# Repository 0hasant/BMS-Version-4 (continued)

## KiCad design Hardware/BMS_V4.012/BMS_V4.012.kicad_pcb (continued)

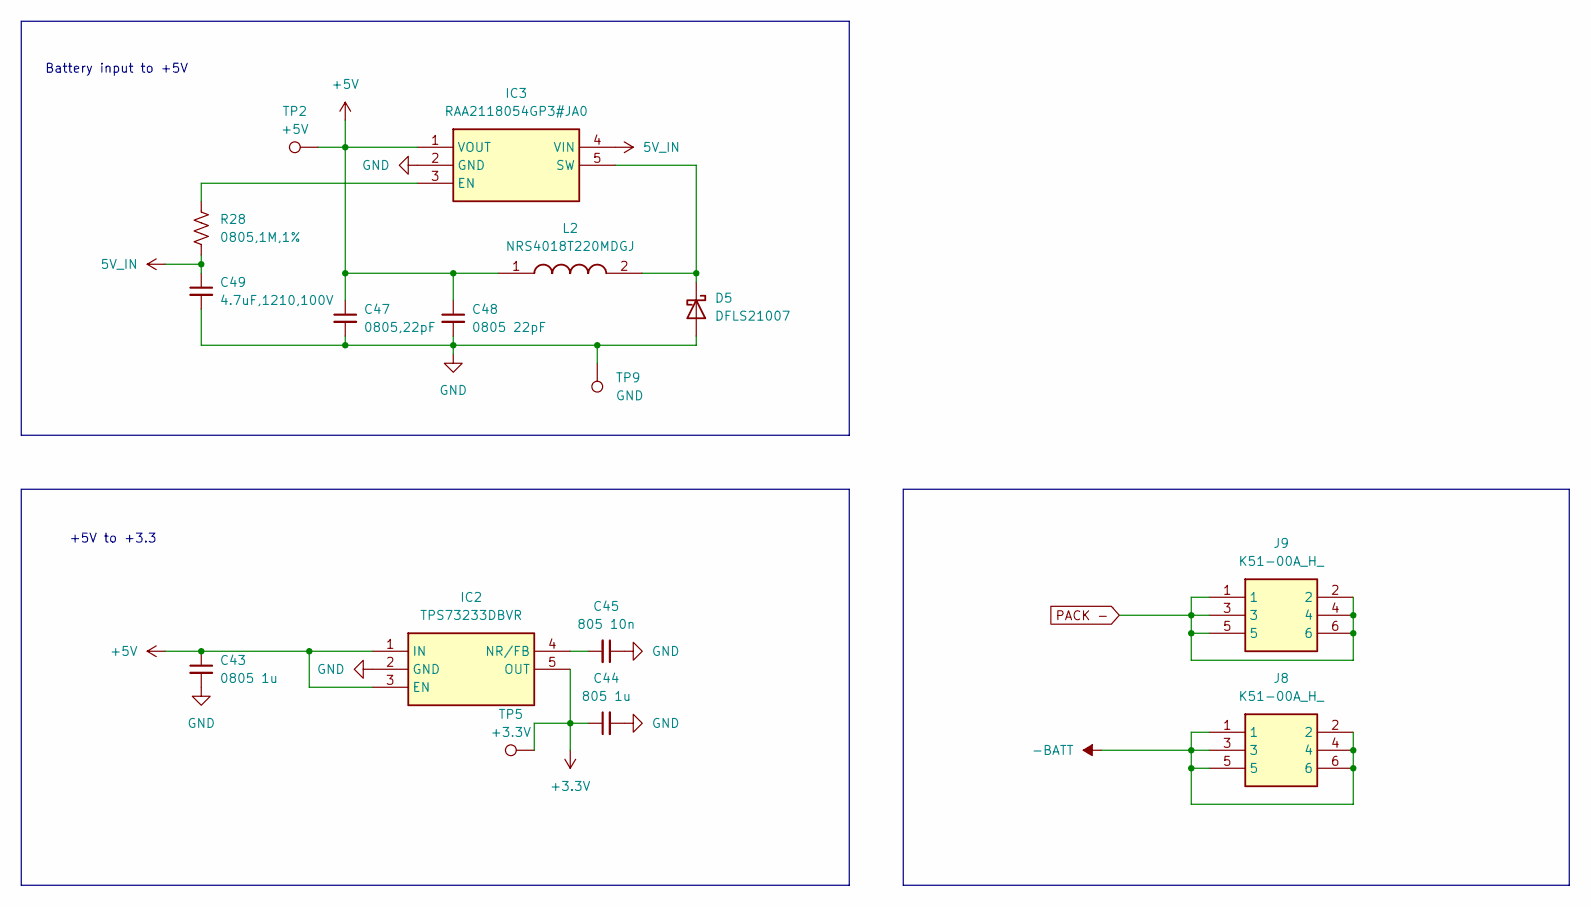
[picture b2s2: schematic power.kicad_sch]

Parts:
C43: 0805 1u; CAPC2012X94N
C44: 805 1u; CAPC2012X94N
C45: 805 10n; CAPC2012X94N
C47: 0805,22pF; CAPC2012X94N
C48: 0805 22pF; CAPC2012X94N
C49: 4.7uF,1210,100V; C_1210_3225Metric
D5: DFLS21007
IC2: TPS73233DBVR; SOT95P280X145-5N; Manufacturer_Part_Number TPS73233DBVR; Mouser Part Number 595-TPS73233DBVR
IC3: RAA2118054GP3#JA0; SOT95P280X110-5N; Manufacturer_Part_Number RAA2118054GP3#JA0; Mouser Part Number 968-RAA2118054GP3JA0
J8, J9: K51-00A_H_; K5100AH; Manufacturer_Part_Number K51-00A(H)
L2: NRS4018T220MDGJ; Manufacturer_Part_Number NRS4018T220MDGJ; Mouser Part Number 963-NRS4018T220MDGJ
R28: 0805,1M,1%; RES_ERA6AHD330V
TP2: +5V; TestPoint_THTPad_D1.0mm_Drill0.5mm
TP5: +3.3V; TestPoint_THTPad_D1.0mm_Drill0.5mm
TP9: GND; TestPoint_2Pads_Pitch5.08mm_Drill1.3mm

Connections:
5V_IN: C49.1, IC3.4 (VIN), R28.2; also elsewhere on the board
+3.3V: C44.1, IC2.5 (OUT), TP5.1; also elsewhere on the board
+5V: C43.1, C47.1, C48.1, IC2.1 (IN), IC2.3 (EN), IC3.1 (VOUT), L2.1, TP2.1; also elsewhere on the board
-BATT: J8.1, J8.2, J8.3, J8.4, J8.5, J8.6; also elsewhere on the board
GND: C43.2, C44.2, C45.1, C47.2, C48.2, C49.2, D5.2 (A), IC2.2 (GND), IC3.2 (GND), TP9.1; also elsewhere on the board
unnamed: D5.1 (K), IC3.5 (SW), L2.2
unnamed: C45.2, IC2.4 (NR/FB)
unnamed: IC3.3 (EN), R28.1
PACK -: J9.1, J9.2, J9.3, J9.4, J9.5, J9.6; also elsewhere on the board

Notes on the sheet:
+5V to +3.3
Battery input to +5V

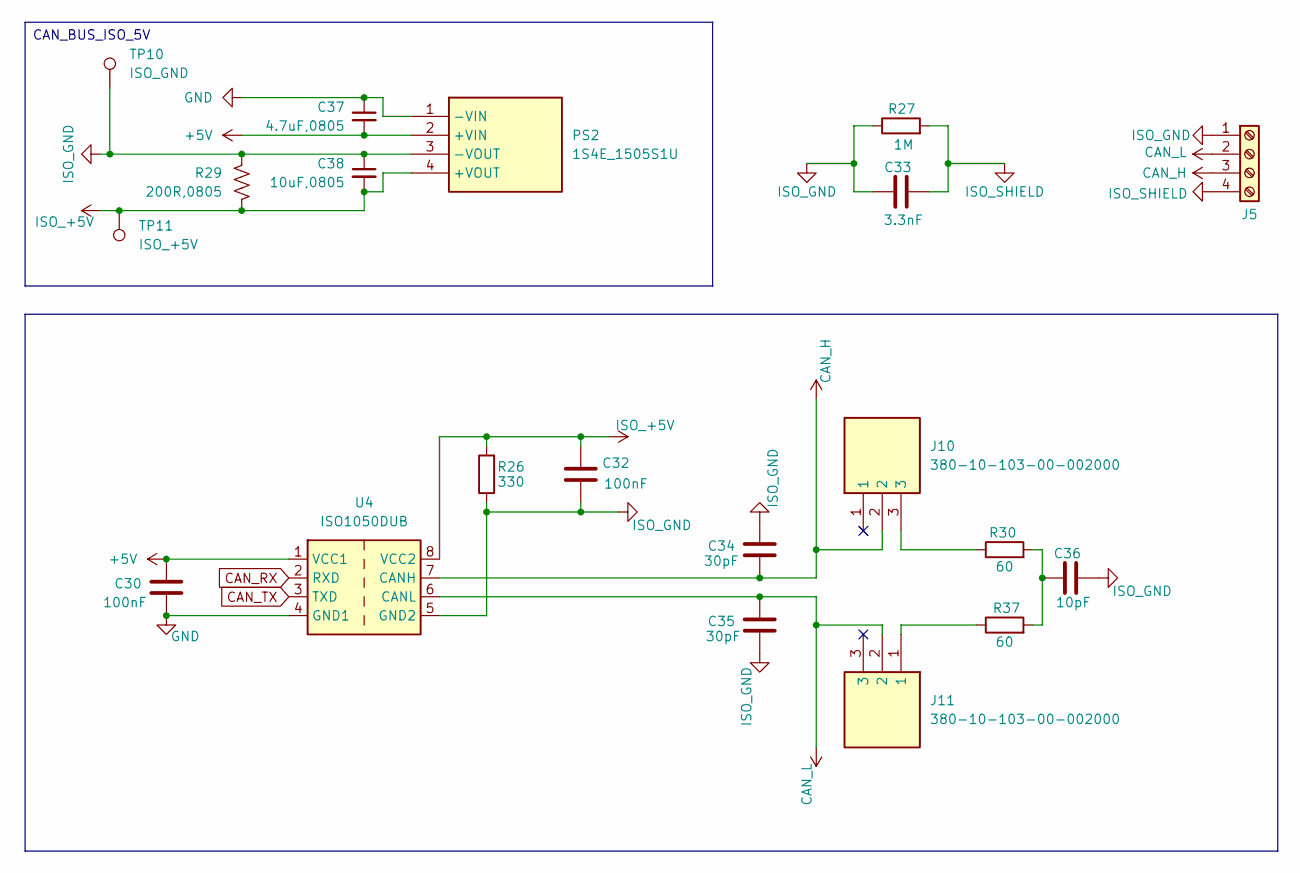
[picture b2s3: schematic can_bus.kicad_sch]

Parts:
C30, C32: 100nF; C_0805_2012Metric_Pad1.18x1.45mm_HandSolder
C33: 3.3nF; C_Disc_D10.5mm_W5.0mm_P5.00mm
C34, C35: 30pF; C_0805_2012Metric_Pad1.18x1.45mm_HandSolder
C36: 10pF; C_0805_2012Metric_Pad1.18x1.45mm_HandSolder
C37: 4.7uF,0805; CAPC2012X94N
C38: 10uF,0805; CAPC2012X94N
J5: Screw_Terminal_01x04; TerminalBlock_Phoenix_MKDS-1,5-4-5.08_1x04_P5.08mm_Horizont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
J10, J11: 380-10-103-00-002000; HDRV3W51P0X254_1X3_762X254X470P; Manufacturer_Part_Number 380-10-103-00-002000; Mouser Part Number 575-3801010300002000
PS2: 1S4E_1505S1U; 1S4E_0303S1U; Manufacturer_Part_Number 1S4E_1505S1U
R26: 330; R_0805_2012Metric_Pad1.20x1.40mm_HandSolder
R27: 1M; R_0805_2012Metric_Pad1.20x1.40mm_HandSolder
R29: 200R,0805; LED_0805_2012Metric_Pad1.15x1.40mm_HandSolder
R30, R37: 60; R_0805_2012Metric_Pad1.20x1.40mm_HandSolder
TP10: ISO_GND; TestPoint_THTPad_D1.0mm_Drill0.5mm
TP11: ISO_+5V; TestPoint_THTPad_D1.0mm_Drill0.5mm
U4: ISO1050DUB; SOP-8_6.62x9.15mm_P2.54mm

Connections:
+5V: C30.1, C37.2, PS2.2 (+VIN), U4.1 (VCC1); also elsewhere on the board
CAN_H: C34.2, J5.3, J10.2, U4.7 (CANH)
CAN_L: C35.1, J5.2, J11.2, U4.6 (CANL)
CAN_RX: U4.2 (RXD); also elsewhere on the board
CAN_TX: U4.3 (TXD); also elsewhere on the board
GND: C30.2, C37.1, PS2.1 (-VIN), U4.4 (GND1); also elsewhere on the board
ISO_+5V: C32.1, C38.2, PS2.4 (+VOUT), R26.2, R29.2, TP11.1, U4.8 (VCC2)
ISO_GND: C32.2, C33.1, C34.1, C35.2, C36.2, C38.1, J5.1, PS2.3 (-VOUT), R26.1, R27.1, R29.1, TP10.1, U4.5 (GND2)
ISO_SHIELD: C33.2, J5.4, R27.2
unnamed: C36.1, R30.2, R37.2
unnamed: J10.3, R30.1
unnamed: J11.1, R37.1

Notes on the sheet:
CAN_BUS_ISO_5V

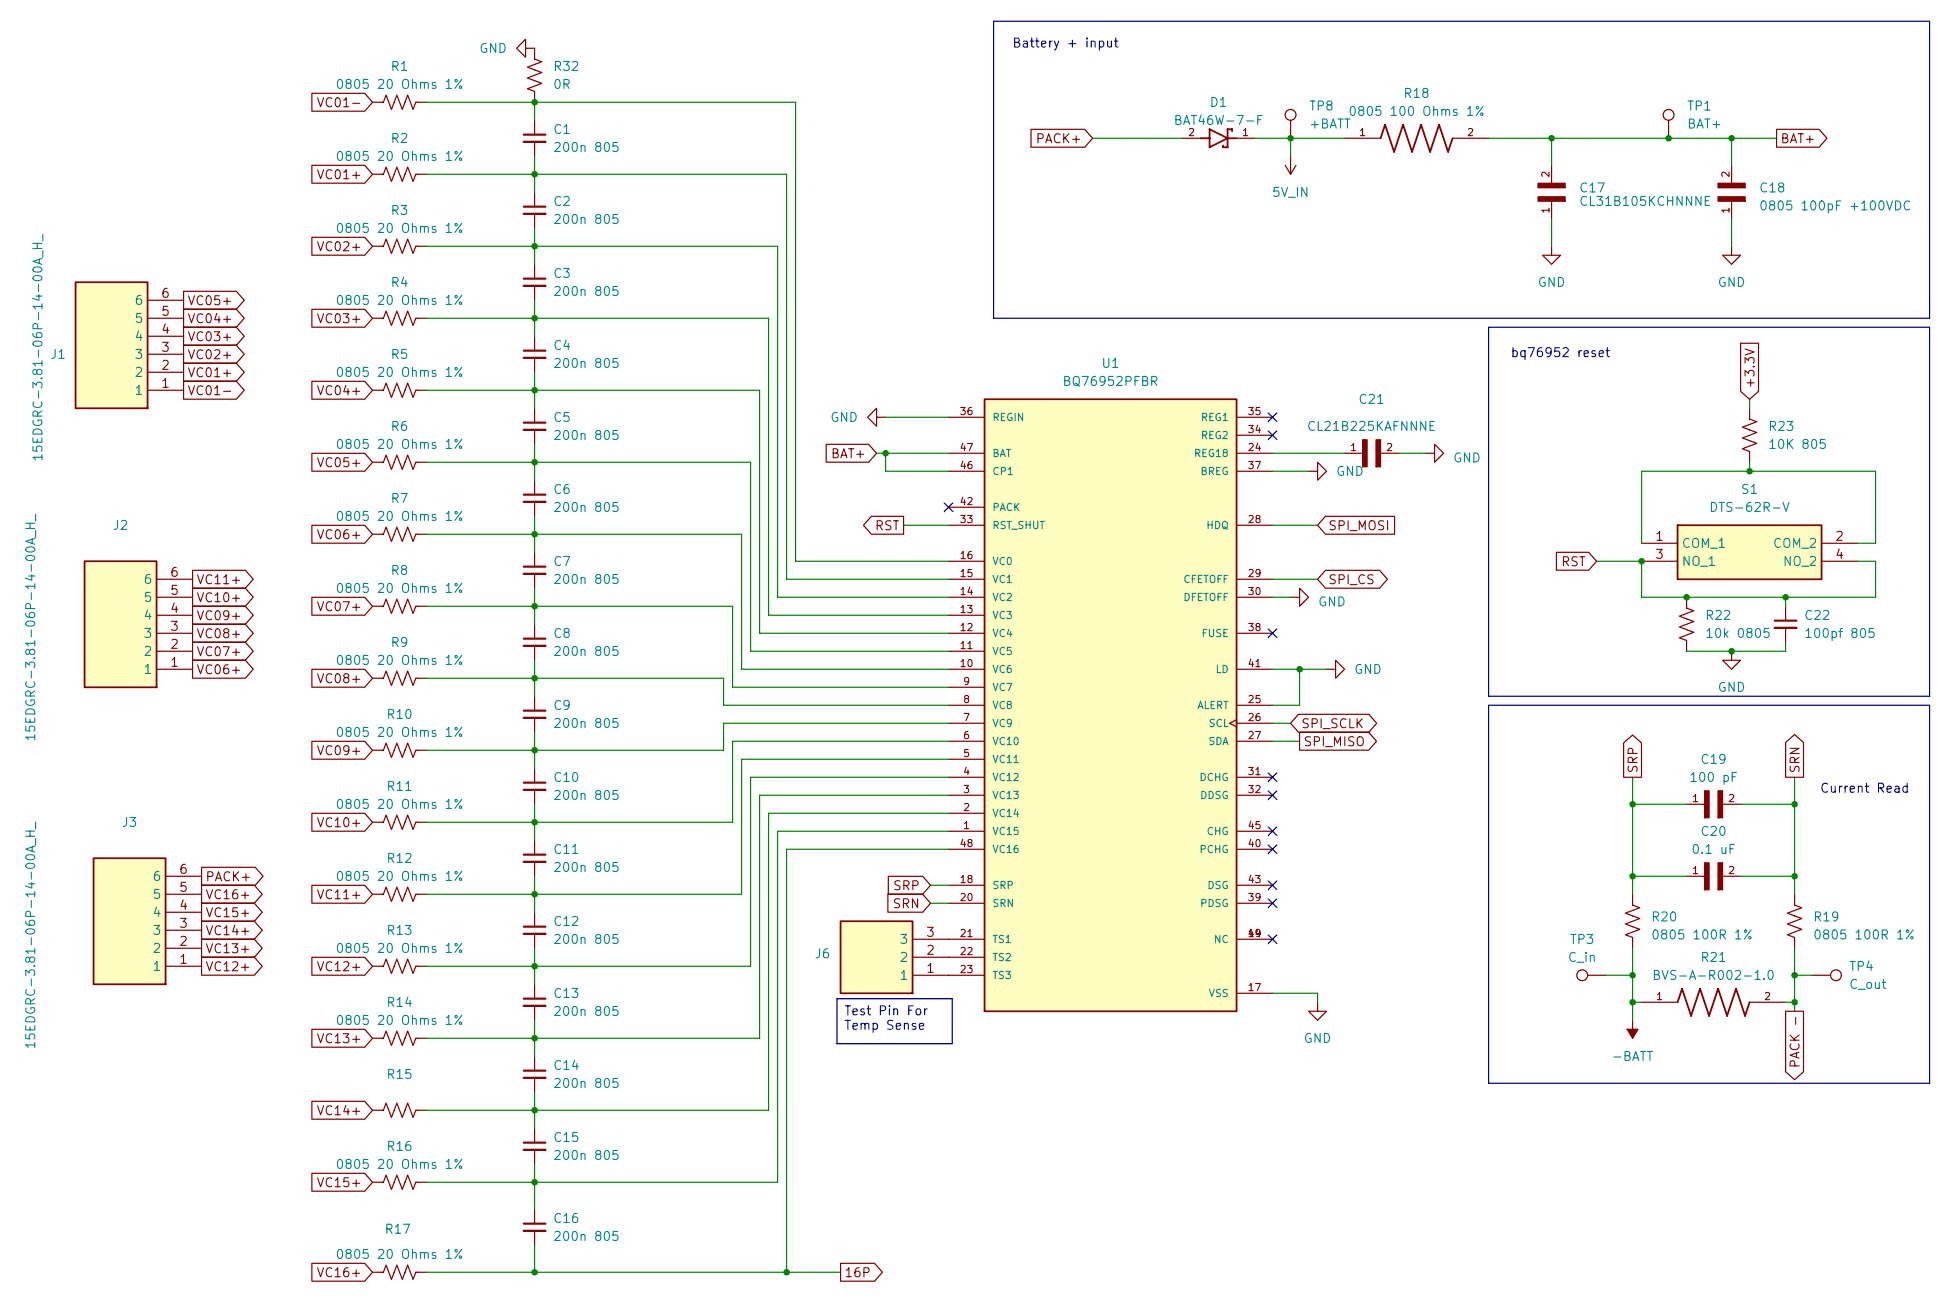
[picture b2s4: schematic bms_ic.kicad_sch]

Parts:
C1, C2, C3, C4, C5, C6, C7, C8, C9, C10, C11, C12, C13, C14, C15, C16: 200n 805; C_0805_2012Metric
C17: CL31B105KCHNNNE; CAPC3216X180N
C18: 0805 100pF +100VDC; CAPC2012X94N
C19: 100 pF; CAPC2012X94N
C20: 0.1 uF; CAPC2012X94N
C21: CL21B225KAFNNNE; CAPC2012X94N
C22: 100pf 805; CAPC2012X94N
D1: BAT46W-7-F; SOD3715X145N; PARTREV 18 - 2
J1, J2, J3: 15EDGRC-3.81-06P-14-00A_H_; SHDRRA6W80P0X381_1X6_2365X920X754P; Manufacturer_Part_Number 15EDGRC-3.81-06P-14-00A(H)
J6: 380-10-103-00-002000; HDRV3W51P0X254_1X3_762X254X470P; Manufacturer_Part_Number 380-10-103-00-002000; Mouser Part Number 575-3801010300002000
R1, R2, R3, R4, R5, R6, R7, R8, R9, R10, R11, R12, R13, R14, R15, R16, R17: 0805 20 Ohms 1%; RESC2012X70N
R18: 0805 100 Ohms 1%; RES_ERA6AHD330V; PARTREV 3/1/2020
R19, R20: 0805 100R 1%; RES_ERA6AHD330V
R21: BVS-A-R002-1.0; RESC10052X125N
R22: 10k 0805; RES_ERA6AHD330V
R23: 10K 805; RES_ERA6AHD330V
R32: 0R; RESC2012X70N
S1: DTS-62R-V; DTS62RV; Manufacturer_Part_Number DTS-62R-V; Mouser Part Number 113-DTS62RV
TP1: BAT+; TestPoint_THTPad_D1.0mm_Drill0.5mm
TP3: C_in; TestPoint_THTPad_D1.0mm_Drill0.5mm
TP4: C_out; TestPoint_THTPad_D1.0mm_Drill0.5mm
TP8: +BATT; TestPoint_THTPad_D1.0mm_Drill0.5mm
U1: BQ76952PFBR; QFP50P900X900X120-48N; PARTREV B

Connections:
5V_IN: D1.1, R18.1, TP8.1; also elsewhere on the board
16P: C16.2, R17.2, U1.48 (VC16)
+3.3V: R23.1; also elsewhere on the board
-BATT: R20.2, R21.1, TP3.1; also elsewhere on the board
BAT+: C17.2, C18.2, R18.2, TP1.1, U1.46 (CP1), U1.47 (BAT)
GND: C17.1, C18.1, C21.2, C22.2, R22.1, R32.1, U1.17 (VSS), U1.25 (ALERT), U1.30 (DFETOFF), U1.36 (REGIN), U1.37 (BREG), U1.41 (LD); also elsewhere on the board
unnamed: R23.2, S1.1 (COM_1), S1.2 (COM_2)
unnamed: C21.1, U1.24 (REG18)
unnamed: J6.3, U1.21 (TS1)
unnamed: J6.2, U1.22 (TS2)
unnamed: J6.1, U1.23 (TS3)
unnamed: C1.1, R1.2, R32.2, U1.16 (VC0)
unnamed: C1.2, C2.1, R2.2, U1.15 (VC1)
unnamed: C2.2, C3.1, R3.2, U1.14 (VC2)
unnamed: C3.2, C4.1, R4.2, U1.13 (VC3)
unnamed: C4.2, C5.1, R5.2, U1.12 (VC4)
unnamed: C5.2, C6.1, R6.2, U1.11 (VC5)
unnamed: C6.2, C7.1, R7.2, U1.10 (VC6)
unnamed: C7.2, C8.1, R8.2, U1.9 (VC7)
unnamed: C8.2, C9.1, R9.2, U1.8 (VC8)
unnamed: C9.2, C10.1, R10.2, U1.7 (VC9)
unnamed: C10.2, C11.1, R11.2, U1.6 (VC10)
unnamed: C11.2, C12.1, R12.2, U1.5 (VC11)
unnamed: C12.2, C13.1, R13.2, U1.4 (VC12)
unnamed: C13.2, C14.1, R14.2, U1.3 (VC13)
unnamed: C14.2, C15.1, R15.2, U1.2 (VC14)
unnamed: C15.2, C16.1, R16.2, U1.1 (VC15)
PACK -: R19.2, R21.2, TP4.1; also elsewhere on the board
PACK+: D1.2, J3.6
RST: C22.1, R22.2, S1.3 (NO_1), S1.4 (NO_2), U1.33 (RST_SHUT)
SPI_CS: U1.29 (CFETOFF); also elsewhere on the board
SPI_MISO: U1.27 (SDA); also elsewhere on the board
SPI_MOSI: U1.28 (HDQ); also elsewhere on the board
SPI_SCLK: U1.26 (SCL); also elsewhere on the board
SRN: C19.2, C20.2, R19.1, U1.20 (SRN)
SRP: C19.1, C20.1, R20.1, U1.18 (SRP)
VC01+: J1.2, R2.1
VC01-: J1.1, R1.1
VC02+: J1.3, R3.1
VC03+: J1.4, R4.1
VC04+: J1.5, R5.1
VC05+: J1.6, R6.1
VC06+: J2.1, R7.1
VC07+: J2.2, R8.1
VC08+: J2.3, R9.1
VC09+: J2.4, R10.1
VC10+: J2.5, R11.1
VC11+: J2.6, R12.1
VC12+: J3.1, R13.1
VC13+: J3.2, R14.1
VC14+: J3.3, R15.1
VC15+: J3.4, R16.1
VC16+: J3.5, R17.1

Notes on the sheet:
Current Read
bq76952 reset
Battery + input
Test Pin For Temp Sense

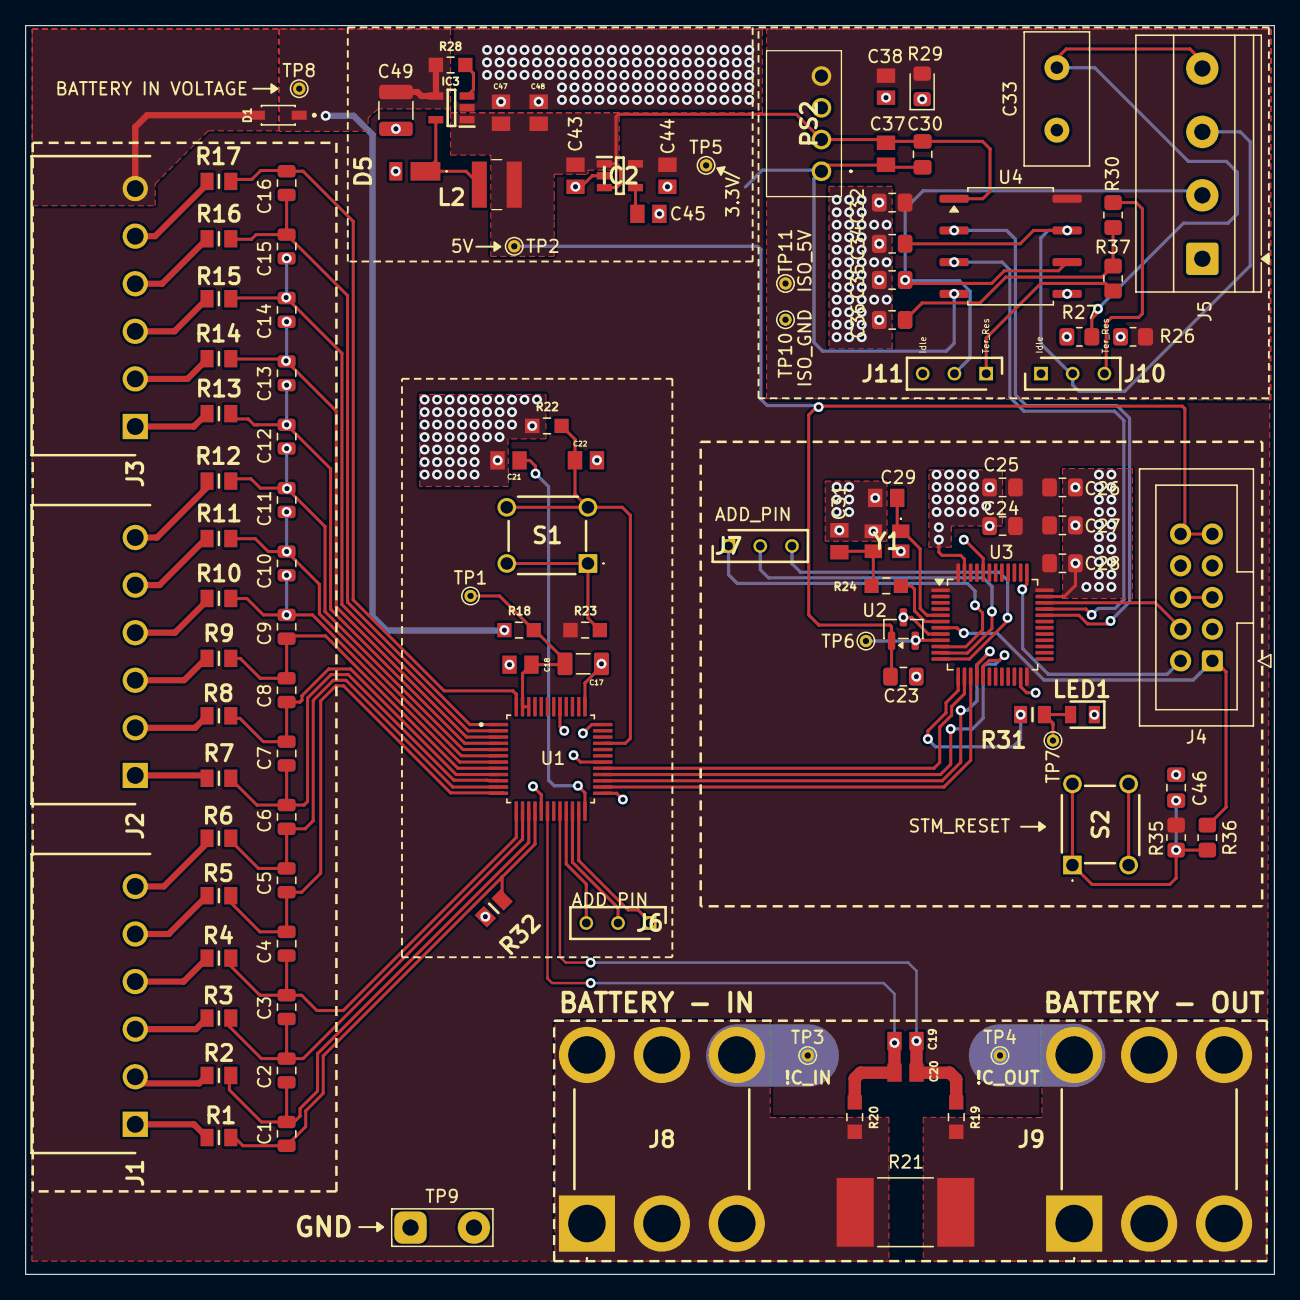
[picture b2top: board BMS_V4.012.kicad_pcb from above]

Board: 2 copper layers, 100.0 x 100.0 mm, 116 parts (1 on the bottom side), 81 nets.

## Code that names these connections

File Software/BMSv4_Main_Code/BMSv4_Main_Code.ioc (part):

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Mcu.Name=STM32F103C(8-B)Tx
Mcu.Package=LQFP48
Mcu.UserName=STM32F103C8Tx
PA0-WKUP.GPIOParameters=GPIO_Label
PA0-WKUP.GPIO_Label=Temp
PA0-WKUP.Signal=ADCx_IN0
PA11.Mode=CAN_Activate
PA11.Signal=CAN_RX
PA12.Mode=CAN_Activate
PA12.Signal=CAN_TX
PA13.Mode=Serial_Wire
PA13.Signal=SYS_JTMS-SWDIO
PA14.Mode=Serial_Wire
PA14.Signal=SYS_JTCK-SWCLK
PA3.GPIOParameters=GPIO_Label
PA3.GPIO_Label=LED
PA3.Signal=GPIO_Output
PA4.GPIOParameters=PinState,GPIO_Label
PA4.GPIO_Label=CS
PA4.PinState=GPIO_PIN_SET
PA4.Signal=GPIO_Output
PA5.Mode=Full_Duplex_Master
PA5.Signal=SPI1_SCK
PA6.Mode=Full_Duplex_Master
PA6.Signal=SPI1_MISO
PA7.Mode=Full_Duplex_Master
PA7.Signal=SPI1_MOSI
PB10.GPIOParameters=GPIO_Label
PB10.GPIO_Label=BMS_NUM1
PB10.Signal=GPIO_Output
PB11.GPIOParameters=GPIO_Label
PB11.GPIO_Label=BMS_NUM2
PB11.Signal=GPIO_Output
PB12.GPIOParameters=GPIO_Label
PB12.GPIO_Label=S0
PB12.Signal=GPIO_Output
PB13.GPIOParameters=GPIO_Label
PB13.GPIO_Label=S1
PB13.Signal=GPIO_Output
PB14.GPIOParameters=GPIO_Label
PB14.GPIO_Label=S2
PB14.Signal=GPIO_Output
PB15.GPIOParameters=GPIO_Label
PB15.GPIO_Label=S3
PB15.Signal=GPIO_Output
PB6.Mode=I2C
PB6.Signal=I2C1_SCL
PB7.Mode=I2C
PB7.Signal=I2C1_SDA
PB8.GPIOParameters=GPIO_Label
PB8.GPIO_Label=Balance_Enable
PB8.Signal=GPIO_Output
PD0-OSC_IN.Mode=HSE-External-Clock-Source
PD0-OSC_IN.Signal=RCC_OSC_IN
PD1-OSC_OUT.Mode=HSE-External-Clock-Source
PD1-OSC_OUT.Signal=RCC_OSC_OUT
RCC.SYSCLKFreq_VALUE=16000000
RCC.SYSCLKSource=RCC_SYSCLKSOURCE_PLLCLK
board=custom

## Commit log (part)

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2026-04-25 Old version are removed
    To keep it simple the manual added version history are deleted. Can be found locally.
2026-04-25 Add project title to README
2026-04-25 Name changed
    The name of Ki-Cad file change from V4.013 to V4.
2026-04-25 Datahseets and Lists are added
2026-04-25 Not important files deleted
2026-04-25 PACK Pin Connection
    The PACK pin of BQ connected via 10k resistor to BAT+
2026-04-25 Create pr-kicad-diff.yml.txt
    Add Kiri GitHub Action for automated visual diffs
2026-04-25 Trace optimization
2026-04-25 Visual reperesenation setting of ki-cad
2026-04-25 Trace optimization test
2026-04-26 Name standartization
    The file name of stm32code changed and kicad revison is uptadet
2026-04-26 Document Optimizations
2026-04-26 Cell Connections Sub Sheet Added
    Hiarchical sheet have been tried to implement. New section added to kicad schematic.
2026-04-26 Small Adjustment
2026-04-26 Library for bq76952 is created.
    The library created with basic functions. 7 cells reading logic and bypass shot circuit cell is added.
2026-04-27 Stack Voltage Function Added
2026-04-27 BQ internal temp reading added
2026-05-01 Unnecesary
2026-05-01 The read and write logic of spi changed
2026-05-01 Current reading functions added
2026-05-02 Rest System changed for bq
    The reset button of bq76965 have changed like stm32
2026-05-02 Reset button corected
2026-05-02 Some unnecceceray things
2026-05-03 Code version 1.0.1-Tested Workes
    Version added, started from v1.0.1 for software
    Went back the previus logic functions fır SPI read and write
2026-05-04 Not imp.
2026-05-04 Power Flag Added
    The pcb is updated but there is no change. This is last correction of pcb, after that there will be major change.
2026-05-04 5V Updated- V4.0.21
    A new IC found and used for 5V. The schematic is done.
2026-05-06 Small change after 5V update
2026-05-07 The Cell Reading Function Corrected /Internal balance are tried
2026-05-07 checkout: temporary commit for worktree checkout
2026-05-07 Ballance logic updated-Not tested
2026-05-09 Not Important
2026-05-12 Internal Balance Code Updated
    Min and max temps settings are added
2026-05-12 Balance adj.
2026-05-13 Extrenal Balance Circuit Added
2026-05-16 The safety system add for Contactor
    PhotoMOS system is added but there is not a perfect system for recovery.
2026-05-16 Code Updated for 16Cells-Works
2026-05-18 BMS Numbering button added
2026-05-19 Temp Read ADDED-STM Connection Done
2026-05-19 PCB Routing started
2026-05-19 Balance circuit changed for dublication
2026-05-30 Routing begins
2026-06-03 Routing cnt.
2026-06-03 Routing Cont.
2026-06-04 Rting Cnt
2026-06-17 Routing Cnt
2026-06-18 Routing and Slick screen adj.
